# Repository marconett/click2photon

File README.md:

# click2photon

End-to-end display latency measurement: the time from a mouse click to a visible
change on screen, measured with a photodiode strapped to the monitor.

**How it works:**

- An RP2040 sends a USB HID mouse click
- The color switcher app toggles the screen black/white
- The photodiode picks up the change
- The RP2040 streams ADC samples over serial
- The host logs them to CSV
- `analyze.py` computes the latency

## Components

| Component | Path | Description |
|---|---|---|
| Hardware | `hardware/` | KiCad PCB, breadboard/perfboard layout, and 3D-printable enclosure for the sensor (BPW34 photodiode + TLC271IP transimpedance amplifier). |
| Firmware | `arduino/` | Runs on an Adafruit QT Py RP2040. Fires the mouse click, samples the photodiode (14-bit ADC, 12,000 samples per run), sends results as CSV lines over serial. Flash with `./flash_rp2040.sh`. |
| Host software | `main.py` | Interactive serial terminal. Starts/stops test runs, configures click count and interval, logs device data to `output/*.csv`. |
| Analyzer | `analyze.py` | Computes latency from a session CSV: delta-from-baseline threshold detection, reports per-click latency plus mean/sd/median/min/max. |
| Color switcher | `color-switcher-vulkan/` | C++ Vulkan app that toggles the screen black/white on click, built for minimal rendering latency. Build with `./build_vulkan.sh`, run with `./run_vulkan.sh`. |

## Images

## Host software CLI (`main.py`)

Connects to the device on `/dev/cu.usbmodem101` at 115200 baud and provides an
interactive prompt:

| Command | Description |
|---|---|
| `start` | Start a test session (3s countdown). Logs to `output/<timestamp>_session.csv`. |
| `stop` | Stop the test and close the session CSV. |
| `debug`, `d` | Enable debug mode — device streams raw ADC readings and voltage. |
| `interval <float>`, `i <float>` | Set the time between clicks in seconds (default 0.5). |
| `clicks <int>`, `c <int>` | Set the number of clicks per session (default 10). |
| `connect` / `disconnect` | Open / close the serial connection. |
| `help` | Show the command list. |
| `exit`, `quit` | Disconnect and quit. |

## Usage

```sh
uv sync                     # set up Python environment
./run_vulkan.sh             # start the color switcher on the monitor under test
uv run main.py              # connect to the device, then type: start
uv run analyze.py output/<session>.csv
```

## Similar tools

Multiple similar (and likely better) tools / devices exist:

- [m2p-latency](https://github.com/davidramiro/m2p-latency)
- [Open-Source-LDAT](https://github.com/S4N-T0S/Open-Source-LDAT)
- [OSLTT](https://github.com/OSRTT/OSLTT)

As well as amazing articles detailing the process and results:

- By @farnoy: [Linux latency measurements and compositor tuning](https://farnoy.dev/posts/linux-latency)
- By @davidramiro: [Building an Input Latency Meter (Because ‘Wayland Feels Off’ Isn’t a Metric)](https://davidjusto.com/articles/m2p-latency/)

For fun, I let Claude Fable 5 compare the 4 projects: [COMPARISON.md](./COMPARISON.md).

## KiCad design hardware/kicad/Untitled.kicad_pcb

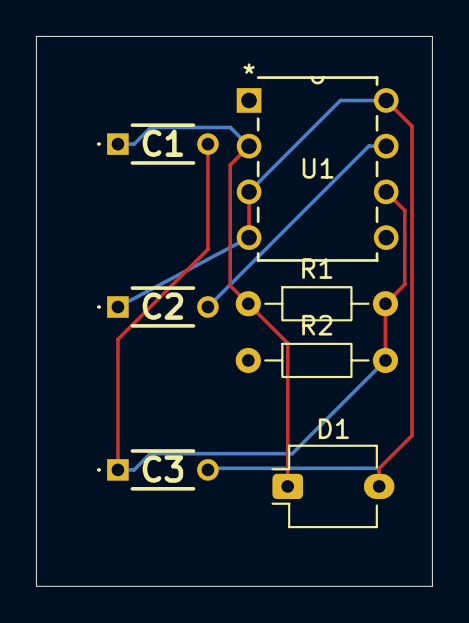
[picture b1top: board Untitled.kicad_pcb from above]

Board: 2 copper layers, 22.0 x 30.5 mm, 7 parts (0 on the bottom side), 4 nets.

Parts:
C1: 1pF; K104K15X7RF53H5G
C2, C3: 100nF; K104K15X7RF53H5G
D1: BPW34; Osram_DIL2_4.3x4.65mm_P5.08mm
R1: 100kΩ; R_Axial_DIN0204_L3.6mm_D1.6mm_P7.62mm_Horizontal
R2: 1kΩ; R_Axial_DIN0204_L3.6mm_D1.6mm_P7.62mm_Horizontal
U1: TLC271IP

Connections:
+3.3V: C2.2, U1.7 (VDD)
GND: C2.1, C3.2, D1.2 (A), U1.3 (IN+), U1.4 (GND), U1.8 (BIASSELECT)
unnamed: C1.1, D1.1 (K), R1.1, U1.2 (IN-)
unnamed: C1.2, C3.1, R1.2, R2.2, U1.6 (OUT)
